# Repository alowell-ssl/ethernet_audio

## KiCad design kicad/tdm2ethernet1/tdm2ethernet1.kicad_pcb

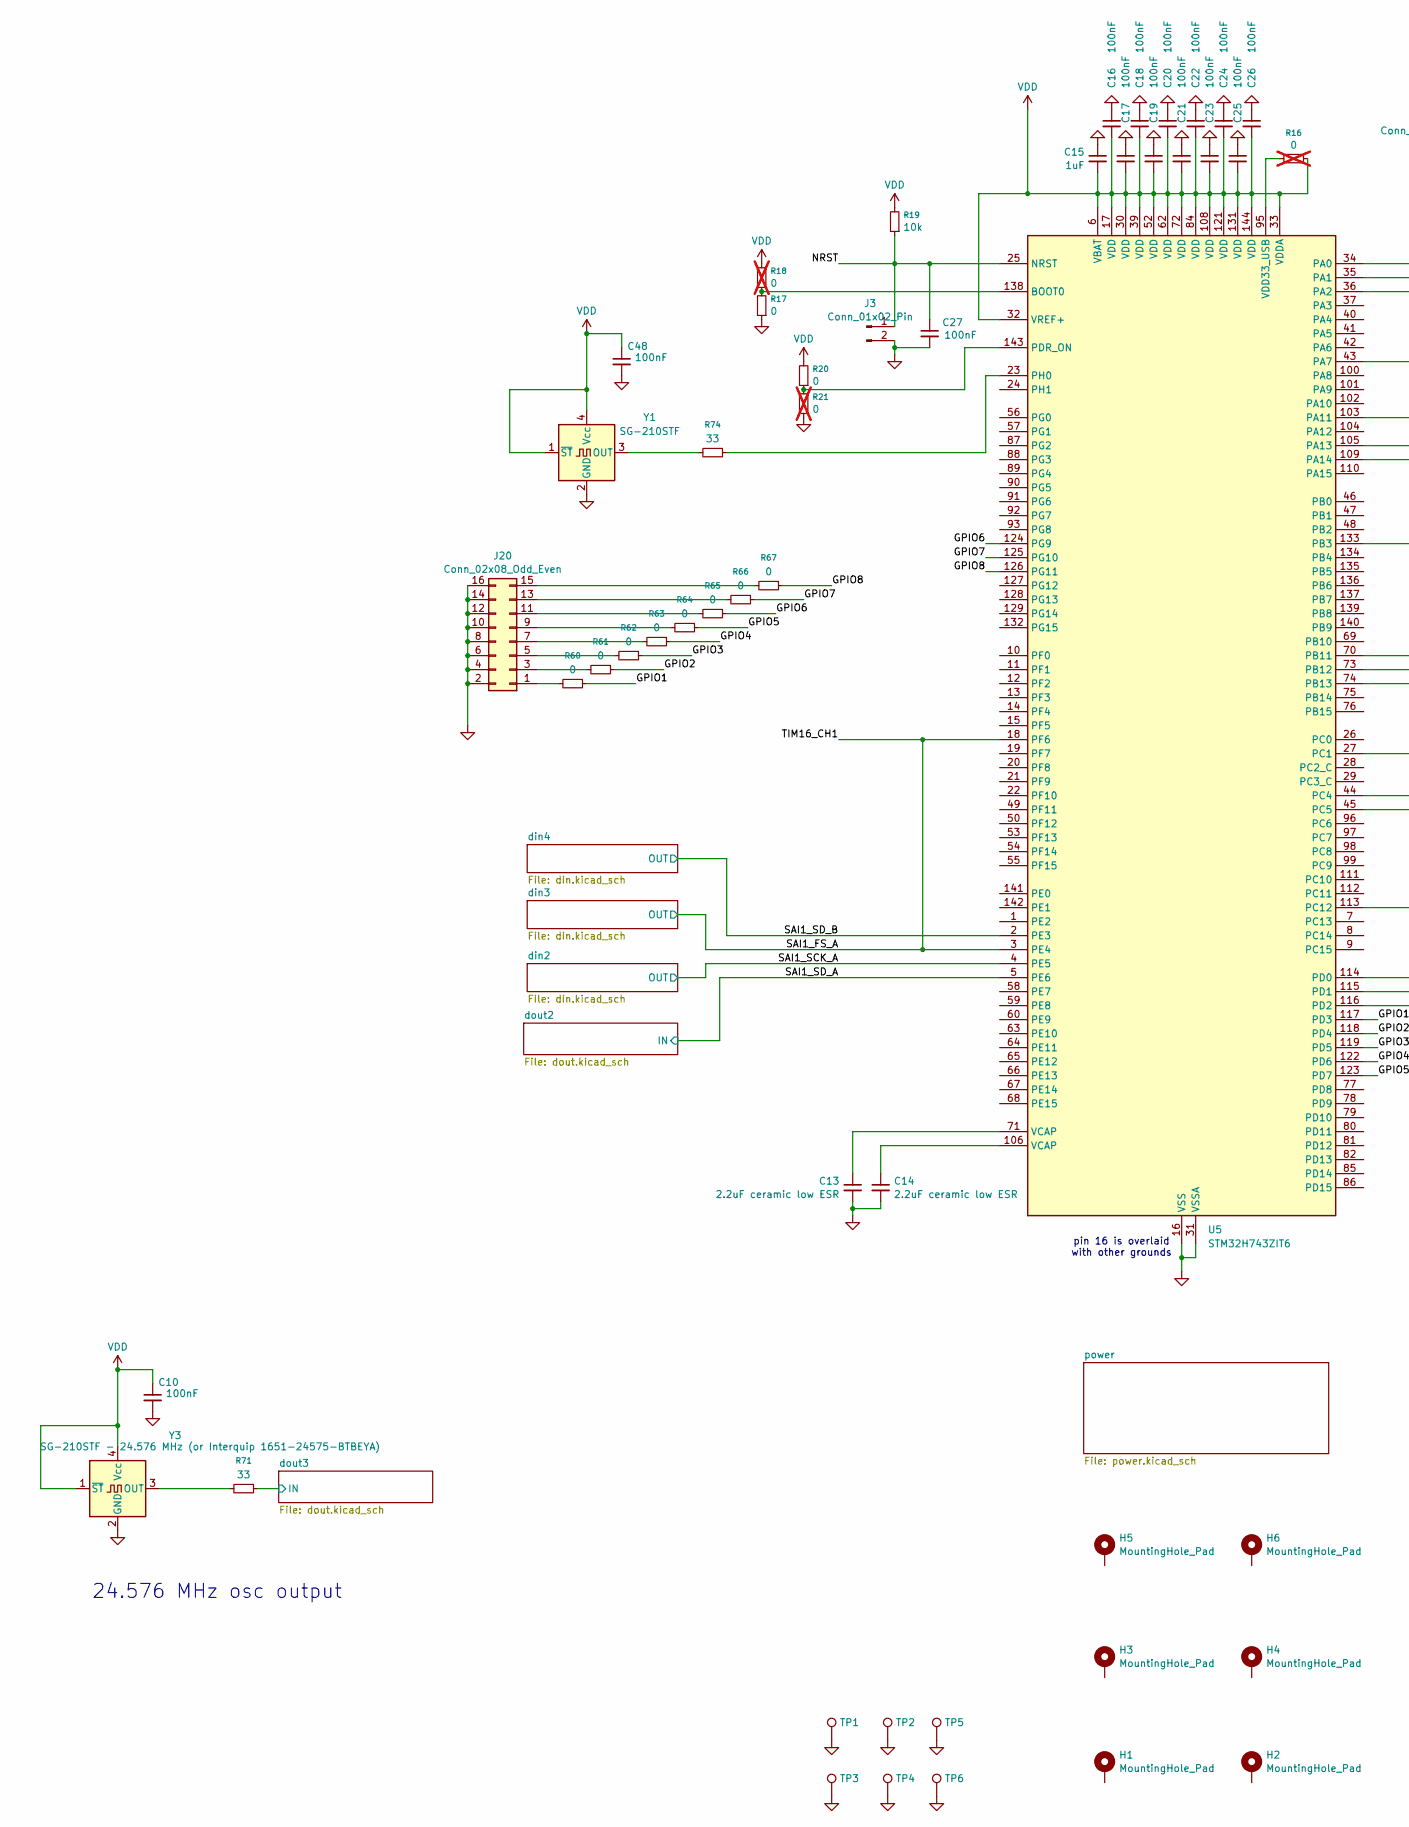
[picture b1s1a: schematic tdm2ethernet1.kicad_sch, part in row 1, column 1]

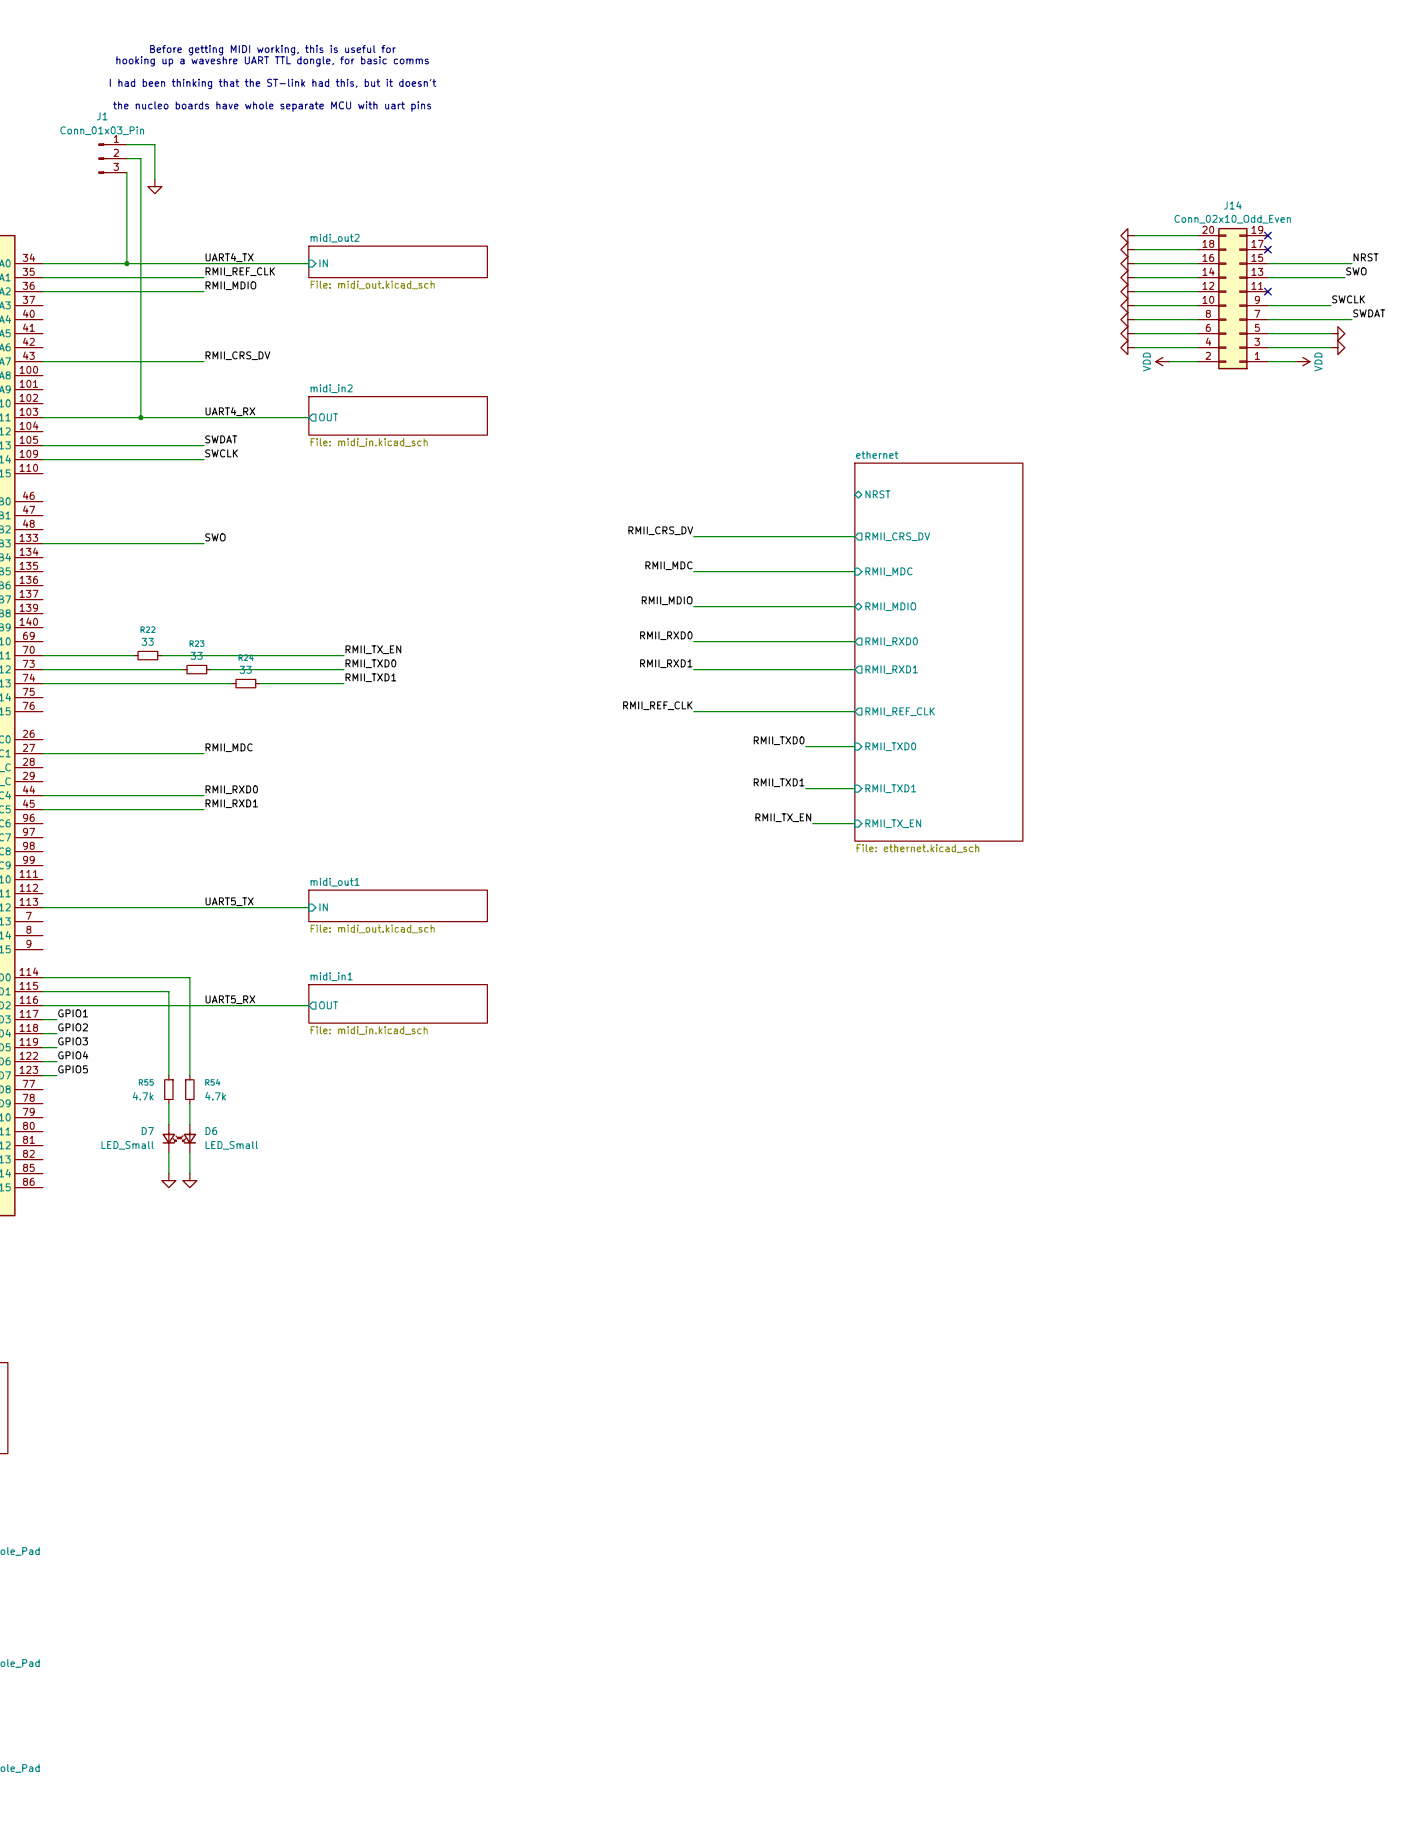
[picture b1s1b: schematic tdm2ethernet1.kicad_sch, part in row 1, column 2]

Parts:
C10, C16, C17, C18, C19, C20, C21, C22, C23, C24, C25, C26, C27, C48: 100nF; C_0603_1608Metric; LCSC Part # C14663
C13, C14: 2.2uF ceramic low ESR; C_0603_1608Metric; LCSC Part # C23630
C15: 1uF; C_0603_1608Metric; LCSC Part # C15849
D6, D7: LED_Small; LED_0603_1608Metric; LCSC Part # C2286
H1, H2, H3, H4, H5, H6: MountingHole_Pad; MountingHole_3.2mm_M3_DIN965
J1: Conn_01x03_Pin; PinHeader_1x03_P2.54mm_Vertical
J3: Conn_01x02_Pin; PinHeader_1x02_P2.54mm_Vertical
J14: Conn_02x10_Odd_Even; PinHeader_2x10_P2.54mm_Vertical
J20: Conn_02x08_Odd_Even; PinSocket_2x08_P2.54mm_Vertical
R16, R18, R21: 0; R_0603_1608Metric; LCSC Part # C21189; not fitted
R17, R20, R60, R61, R62, R63, R64, R65, R66, R67: 0; R_0603_1608Metric; LCSC Part # C21189
R19: 10k; R_0603_1608Metric; LCSC Part # C15401
R22, R23, R24, R71, R74: 33; R_0603_1608Metric; LCSC Part # C23140
R54, R55: 4.7k; R_0603_1608Metric; LCSC Part # C23162
TP1, TP2, TP3, TP4, TP5, TP6: TestPoint; TestPoint_THTPad_D1.5mm_Drill0.7mm
U5: STM32H743ZIT6; LQFP-144_20x20mm_P0.5mm; LCSC Part # C114408
Y1: SG-210STF; Oscillator_SMD_SeikoEpson_SG210-4Pin_2.5x2.0mm; LCSC Part # C70560
Y3: SG-210STF - 24.576 MHz (or Interquip 1651-24575-B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; Oscillator_SMD_SeikoEpson_SG210-4Pin_2.5x2.0mm; LCSC Part # C3003263

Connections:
/GPIO1: R60.1, U5.117 (PD3)
/GPIO2: R61.1, U5.118 (PD4)
/GPIO3: R62.1, U5.119 (PD5)
/GPIO4: R63.1, U5.122 (PD6)
/GPIO5: R64.1, U5.123 (PD7)
/GPIO6: R65.1, U5.124 (PG9)
/GPIO7: R66.1, U5.125 (PG10)
/GPIO8: R67.1, U5.126 (PG11)
/NRST: C27.1, J3.1, J14.15, R19.1, U5.25 (NRST)
/RMII_CRS_DV: U5.43 (PA7); also elsewhere on the board
/RMII_MDC: U5.27 (PC1); also elsewhere on the board
/RMII_MDIO: U5.36 (PA2); also elsewhere on the board
/RMII_REF_CLK: U5.35 (PA1); also elsewhere on the board
/RMII_RXD0: U5.44 (PC4); also elsewhere on the board
/RMII_RXD1: U5.45 (PC5); also elsewhere on the board
/RMII_TXD0: R23.1; also elsewhere on the board
/RMII_TXD1: R24.1; also elsewhere on the board
/RMII_TX_EN: R22.1; also elsewhere on the board
/SAI1_FS_A: U5.3 (PE4), U5.18 (PF6); also elsewhere on the board
/SAI1_SCK_A: U5.4 (PE5); also elsewhere on the board
/SAI1_SD_A: U5.5 (PE6); also elsewhere on the board
/SAI1_SD_B: U5.2 (PE3); also elsewhere on the board
/SWCLK: J14.9, U5.109 (PA14)
/SWDAT: J14.7, U5.105 (PA13)
/SWO: J14.13, U5.133 (PB3)
/UART4_RX: J1.2, U5.103 (PA11); also elsewhere on the board
/UART4_TX: J1.3, U5.34 (PA0); also elsewhere on the board
/UART5_RX: U5.116 (PD2); also elsewhere on the board
/UART5_TX: U5.113 (PC12); also elsewhere on the board
/dout3/IN: R71.1; also elsewhere on the board
GND: C10.2, C13.2, C14.2, C15.1, C16.1, C17.1, C18.1, C19.1, C20.1, C21.1, C22.1, C23.1, C24.1, C25.1, C26.1, C27.2, C48.2, D6.1 (K), D7.1 (K), J1.1, J3.2, J14.3, J14.4, J14.5, J14.6, J14.8, J14.10, J14.12, J14.14, J14.16, J14.18, J14.20, J20.2, J20.4, J20.6, J20.8, J20.10, J20.12, J20.14, J20.16, R17.1, R21.1, TP1.1, TP2.1, TP3.1, TP4.1, TP5.1, TP6.1, U5.16 (VSS), U5.31 (VSSA), U5.38 (VSS), U5.51 (VSS), U5.61 (VSS), U5.83 (VSS), U5.94 (VSS), U5.107 (VSS), U5.120 (VSS), U5.130 (VSS), Y1.2 (GND), Y3.2 (GND); also elsewhere on the board
unnamed: C13.1, U5.71 (VCAP)
unnamed: C14.1, U5.106 (VCAP)
unnamed: D6.2 (A), R54.2
unnamed: D7.2 (A), R55.2
unnamed: J20.1, R60.2
unnamed: J20.3, R61.2
unnamed: J20.5, R62.2
unnamed: J20.7, R63.2
unnamed: J20.9, R64.2
unnamed: J20.11, R65.2
unnamed: J20.13, R66.2
unnamed: J20.15, R67.2
unnamed: R17.2, R18.1, U5.138 (BOOT0)
unnamed: R22.2, U5.70 (PB11)
unnamed: R23.2, U5.73 (PB12)
unnamed: R24.2, U5.74 (PB13)
unnamed: R54.1, U5.114 (PD0)
unnamed: R55.1, U5.115 (PD1)
unnamed: R20.1, R21.2, U5.143 (PDR_ON)
unnamed: R74.1, U5.23 (PH0)
unnamed: R16.1, U5.95 (VDD33_USB)
unnamed: R74.2, Y1.3 (OUT)
unnamed: R71.2, Y3.3 (OUT)
VDD: C10.1, C15.2, C16.2, C17.2, C18.2, C19.2, C20.2, C21.2, C22.2, C23.2, C24.2, C25.2, C26.2, C48.1, J14.1, J14.2, R16.2, R18.2, R19.2, R20.2, U5.6 (VBAT), U5.17 (VDD), U5.30 (VDD), U5.32 (VREF+), U5.33 (VDDA), U5.39 (VDD), U5.52 (VDD), U5.62 (VDD), U5.72 (VDD), U5.84 (VDD), U5.108 (VDD), U5.121 (VDD), U5.131 (VDD), U5.144 (VDD), Y1.1 (~ST), Y1.4 (Vcc), Y3.1 (~ST), Y3.4 (Vcc); also elsewhere on the board

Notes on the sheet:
24.576 MHz osc output
pin 16 is overlaid with other grounds
Before getting MIDI working, this is useful for hooking up a waveshre UART TTL dongle, for basic comms I had been thinking that the ST-link had this, but it doesn't the nucleo boards have whole separate MCU with uart pins

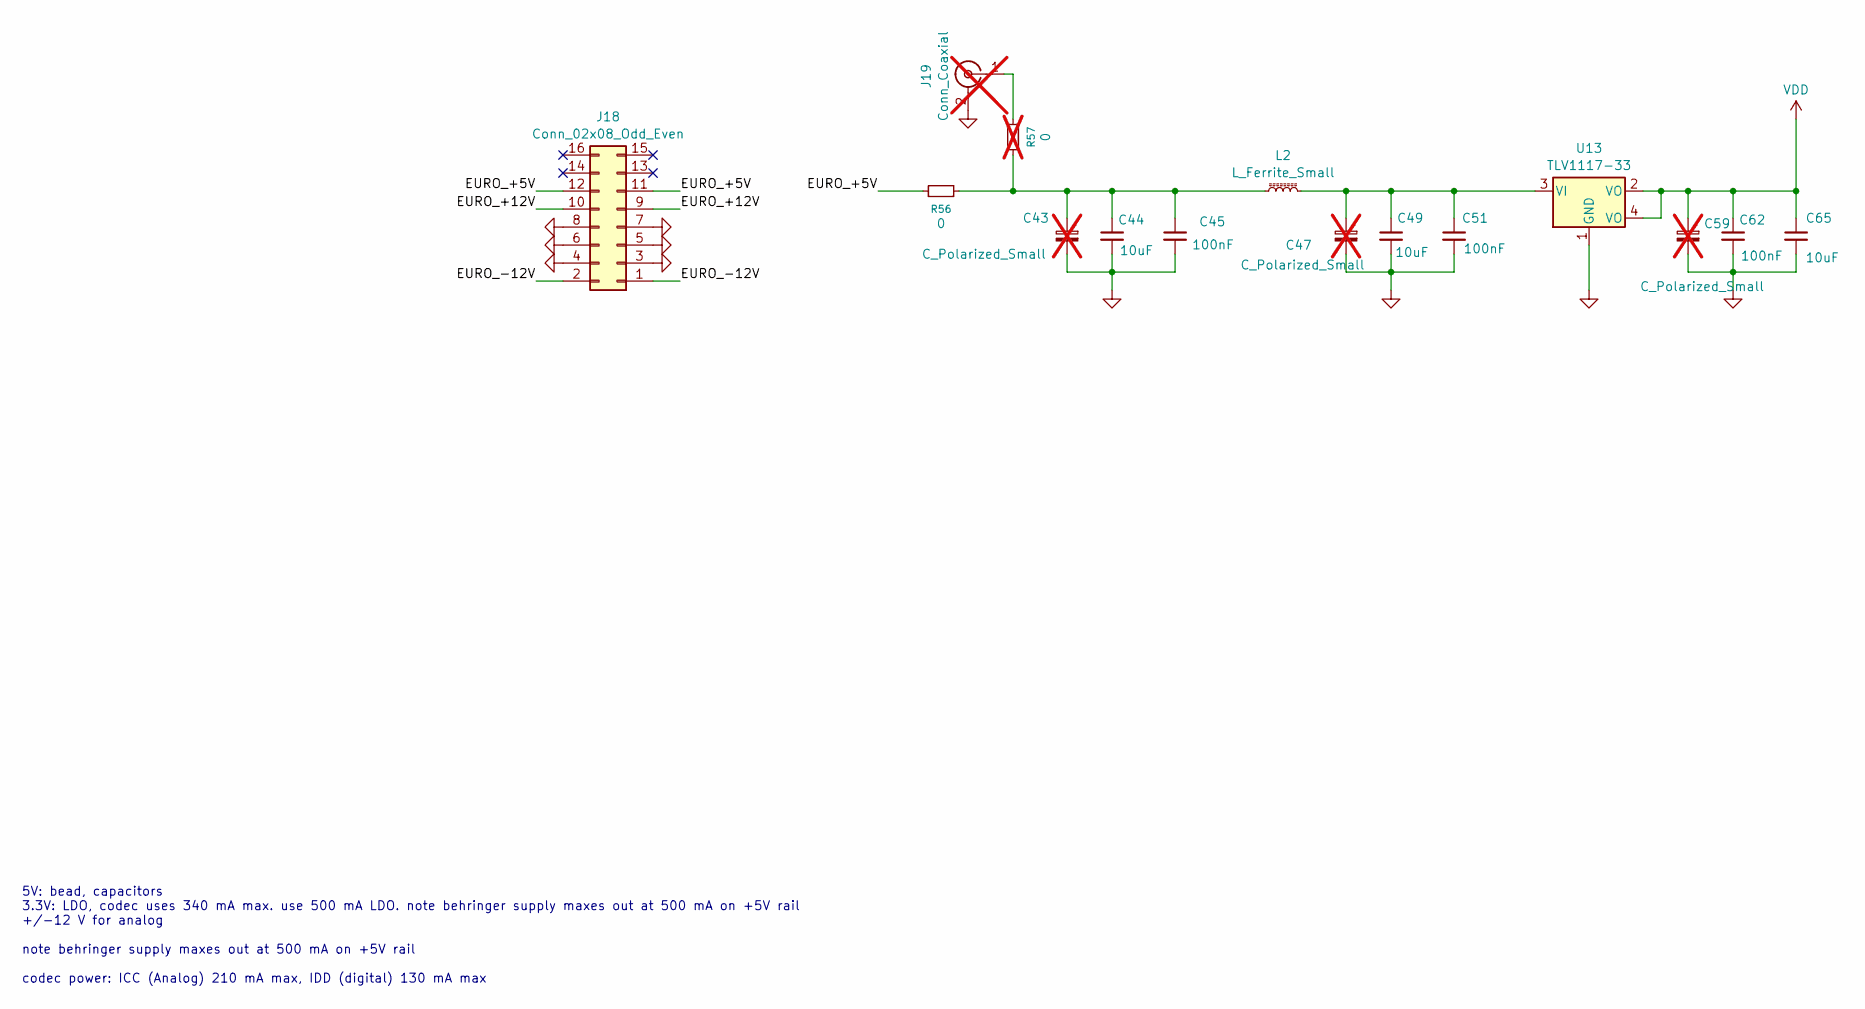
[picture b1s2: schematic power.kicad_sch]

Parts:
C43, C47, C59: C_Polarized_Small; CP_Radial_D8.0mm_P3.50mm; not fitted
C44, C49, C65: 10uF; C_0603_1608Metric; LCSC Part # C96446
C45, C51, C62: 100nF; C_0603_1608Metric; LCSC Part # C14663
J18: Conn_02x08_Odd_Even; PinSocket_2x08_P2.54mm_Vertical
J19: Conn_Coaxial; SMA_Amphenol_901-144_Vertical; not fitted
L2: L_Ferrite_Small; L_0603_1608Metric; LCSC Part # C1002
R56: 0; R_0603_1608Metric; LCSC Part # C21189
R57: 0; R_0603_1608Metric; LCSC Part # C21189; not fitted
U13: TLV1117-33; SOT-223

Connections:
/power/EURO_+5V: J18.11, J18.12, R56.1
/power/EURO_+12V: J18.9, J18.10
/power/EURO_-12V: J18.1, J18.2
GND: C43.2, C44.2, C45.2, C47.2, C49.2, C51.2, C59.2, C62.2, C65.2, J18.3, J18.4, J18.5, J18.6, J18.7, J18.8, J19.2 (Ext), U13.1 (GND); also elsewhere on the board
unnamed: C43.1, C44.1, C45.1, L2.1, R56.2, R57.1
unnamed: J19.1 (In), R57.2
unnamed: C47.1, C49.1, C51.1, L2.2, U13.3 (VI)
VDD: C59.1, C62.1, C65.1, U13.2 (VO), U13.4 (VO); also elsewhere on the board

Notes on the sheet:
5V: bead, capacitors 3.3V: LDO, codec uses 340 mA max. use 500 mA LDO. note behringer supply maxes out at 500 mA on +5V rail +/-12 V for analog note behringer supply maxes out at 500 mA on +5V rail codec power: ICC (Analog) 210 mA max, IDD (digital) 130 mA max

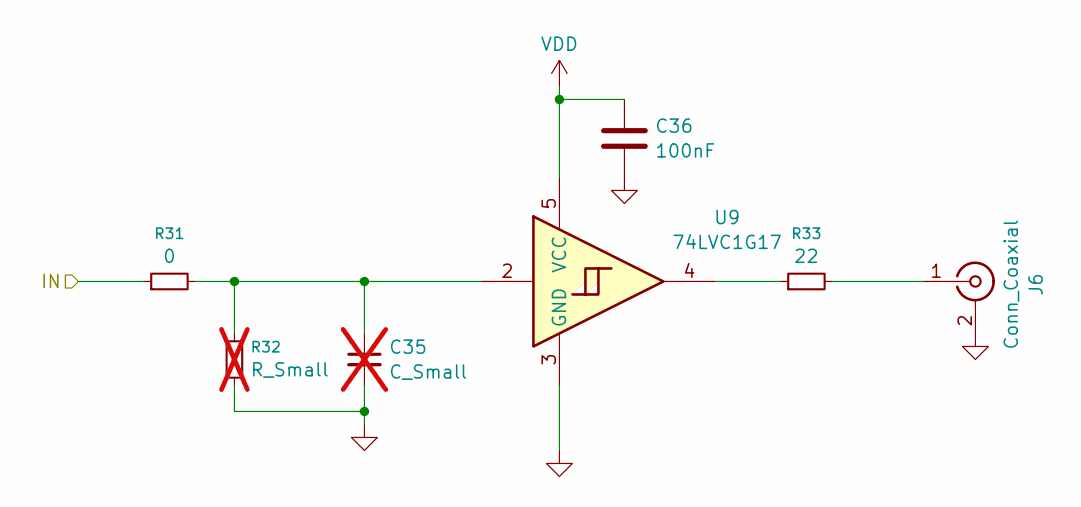
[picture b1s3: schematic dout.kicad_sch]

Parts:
C35: C_Small; C_0603_1608Metric; not fitted
C36: 100nF; C_0603_1608Metric; LCSC Part # C14663
J6: Conn_Coaxial; SMA_Amphenol_901-144_Vertical
R31: 0; R_0603_1608Metric; LCSC Part # C21189
R32: R_Small; R_0603_1608Metric; not fitted
R33: 22; R_0603_1608Metric; LCSC Part # C23345
U9: 74LVC1G17; SOT-23-5; LCSC Part # C7836

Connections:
/SAI1_SD_A: R31.1; also elsewhere on the board
GND: C35.2, C36.2, J6.2 (Ext), R32.1, U9.3 (GND); also elsewhere on the board
unnamed: C35.1, R31.2, R32.2, U9.2
unnamed: J6.1 (In), R33.2
unnamed: R33.1, U9.4
VDD: C36.1, U9.5 (VCC); also elsewhere on the board

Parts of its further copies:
C12: C_Small; C_0603_1608Metric; not fitted
C52: 100nF; C_0603_1608Metric; LCSC Part # C14663
J2: Conn_Coaxial; SMA_Amphenol_901-144_Vertical
R72: 0; R_0603_1608Metric; LCSC Part # C21189
R73: R_Small; R_0603_1608Metric; not fitted
R76: 22; R_0603_1608Metric; LCSC Part # C23345
U14: 74LVC1G17; SOT-23-5; LCSC Part # C7836

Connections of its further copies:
/dout3/IN: R72.1; also elsewhere on the board
GND: C12.2, C52.2, J2.2 (Ext), R73.1, U14.3 (GND); also elsewhere on the board
unnamed: C12.1, R72.2, R73.2, U14.2
unnamed: J2.1 (In), R76.2
unnamed: R76.1, U14.4
VDD: C52.1, U14.5 (VCC); also elsewhere on the board

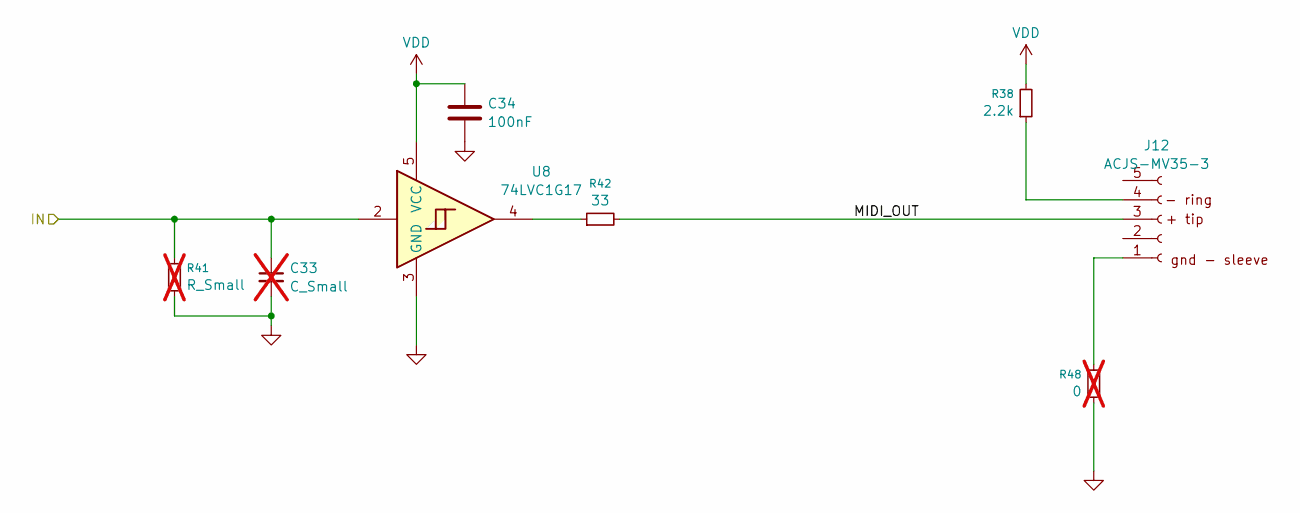
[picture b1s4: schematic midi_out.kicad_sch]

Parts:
C33: C_Small; C_0603_1608Metric; not fitted
C34: 100nF; C_0603_1608Metric; LCSC Part # C14663
J12: ACJS-MV35-3; Amphenol_ACJS
R38: 2.2k; R_0603_1608Metric; LCSC Part # C4190
R41: R_Small; R_0603_1608Metric; not fitted
R42: 33; R_0603_1608Metric; LCSC Part # C23140
R48: 0; R_0603_1608Metric; LCSC Part # C21189; not fitted
U8: 74LVC1G17; SOT-23-5; LCSC Part # C7836

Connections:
/UART5_TX: C33.1, R41.2, U8.2; also elsewhere on the board
/midi_out1/MIDI_OUT: J12.3, R42.2
GND: C33.2, C34.2, R41.1, R48.1, U8.3 (GND); also elsewhere on the board
unnamed: J12.1, R48.2
unnamed: J12.4, R38.1
unnamed: R42.1, U8.4
VDD: C34.1, R38.2, U8.5 (VCC); also elsewhere on the board

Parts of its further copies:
C29: C_Small; C_0603_1608Metric; not fitted
C30: 100nF; C_0603_1608Metric; LCSC Part # C14663
J13: ACJS-MV35-3; Amphenol_ACJS
R28: R_Small; R_0603_1608Metric; not fitted
R29: 33; R_0603_1608Metric; LCSC Part # C23140
R30: 2.2k; R_0603_1608Metric; LCSC Part # C4190
R49: 0; R_0603_1608Metric; LCSC Part # C21189; not fitted
U6: 74LVC1G17; SOT-23-5; LCSC Part # C7836

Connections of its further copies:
/UART4_TX: C29.1, R28.2, U6.2; also elsewhere on the board
/midi_out2/MIDI_OUT: J13.3, R29.2
GND: C29.2, C30.2, R28.1, R49.1, U6.3 (GND); also elsewhere on the board
unnamed: J13.1, R49.2
unnamed: J13.4, R30.1
unnamed: R29.1, U6.4
VDD: C30.1, R30.2, U6.5 (VCC); also elsewhere on the board

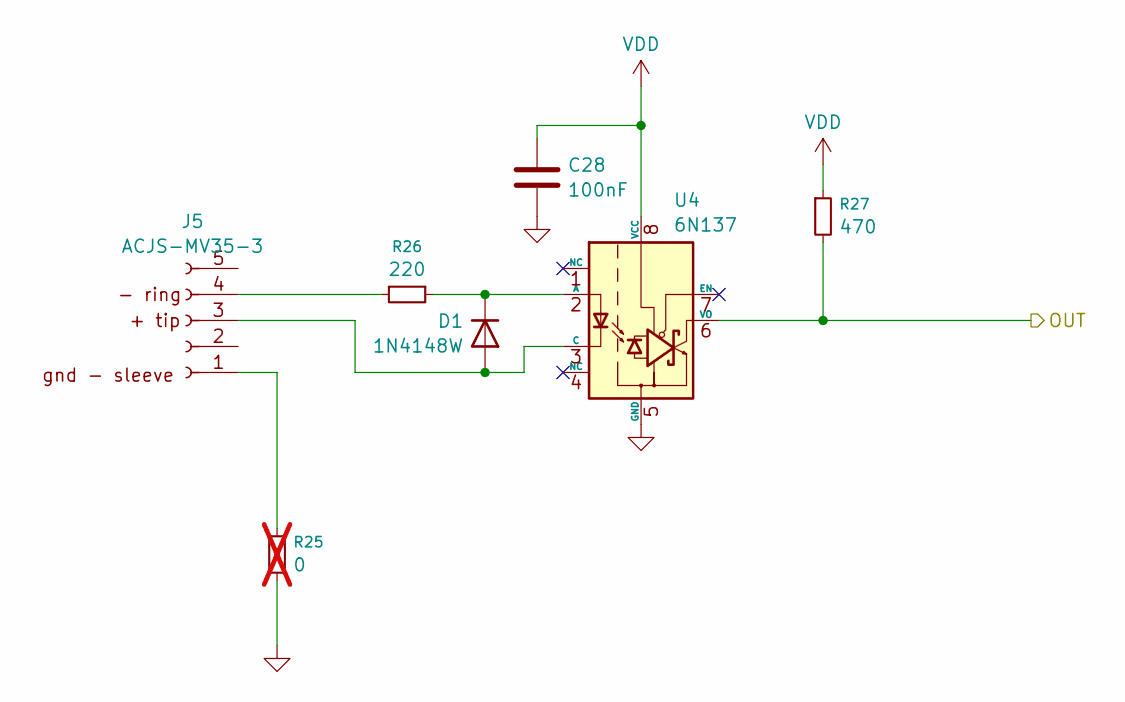
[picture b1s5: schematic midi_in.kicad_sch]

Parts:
C28: 100nF; C_0603_1608Metric; LCSC Part # C14663
D1: 1N4148W; D_SOD-123; LCSC Part # C81598
J5: ACJS-MV35-3; Amphenol_ACJS
R25: 0; R_0603_1608Metric; LCSC Part # C21189; not fitted
R26: 220; R_0603_1608Metric; LCSC Part # C22962
R27: 470; R_0603_1608Metric; LCSC Part # C23179
U4: 6N137; DIP-8_W7.62mm

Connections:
/UART4_RX: R27.2, U4.6 (VO); also elsewhere on the board
GND: C28.2, R25.1, U4.5 (GND); also elsewhere on the board
unnamed: D1.2 (A), J5.3, U4.3 (C)
unnamed: D1.1 (K), R26.1, U4.2 (A)
unnamed: J5.1, R25.2
unnamed: J5.4, R26.2
VDD: C28.1, R27.1, U4.8 (VCC); also elsewhere on the board

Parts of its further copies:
C32: 100nF; C_0603_1608Metric; LCSC Part # C14663
D5: 1N4148W; D_SOD-123; LCSC Part # C81598
J10: ACJS-MV35-3; Amphenol_ACJS
R44: 220; R_0603_1608Metric; LCSC Part # C22962
R45: 470; R_0603_1608Metric; LCSC Part # C23179
R50: 0; R_0603_1608Metric; LCSC Part # C21189; not fitted
U7: 6N137; DIP-8_W7.62mm

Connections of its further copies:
/UART5_RX: R45.2, U7.6 (VO); also elsewhere on the board
GND: C32.2, R50.1, U7.5 (GND); also elsewhere on the board
unnamed: D5.2 (A), J10.3, U7.3 (C)
unnamed: D5.1 (K), R44.1, U7.2 (A)
unnamed: J10.1, R50.2
unnamed: J10.4, R44.2
VDD: C32.1, R45.1, U7.8 (VCC); also elsewhere on the board

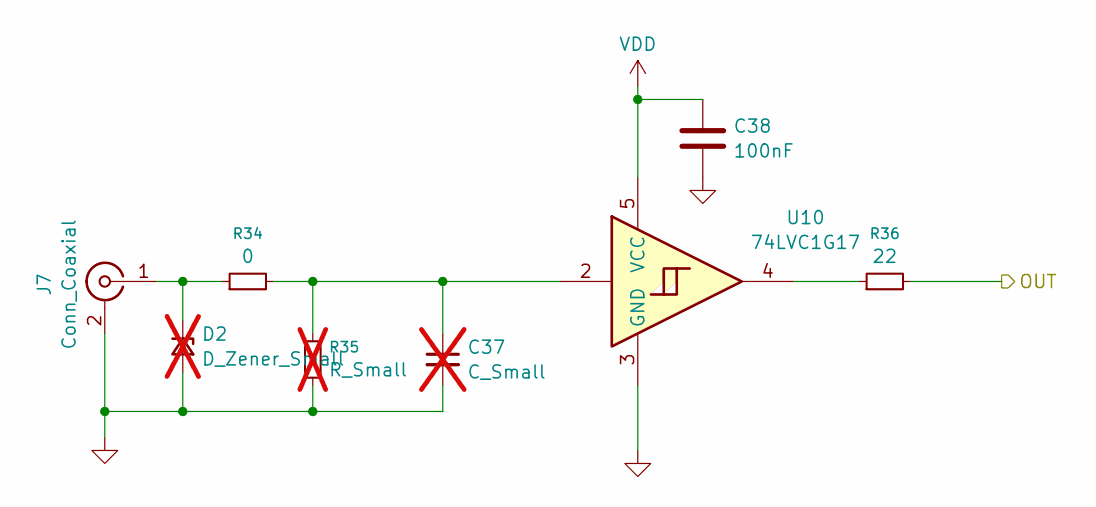
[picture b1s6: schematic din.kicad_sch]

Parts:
C37: C_Small; C_0603_1608Metric; not fitted
C38: 100nF; C_0603_1608Metric; LCSC Part # C14663
D2: D_Zener_Small; D_SOD-123F; not fitted
J7: Conn_Coaxial; SMA_Amphenol_901-144_Vertical
R34: 0; R_0603_1608Metric; LCSC Part # C21189
R35: R_Small; R_0603_1608Metric; not fitted
R36: 22; R_0603_1608Metric; LCSC Part # C23345
U10: 74LVC1G17; SOT-23-5; LCSC Part # C7836

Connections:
/SAI1_SCK_A: R36.2; also elsewhere on the board
GND: C37.2, C38.2, D2.2 (A), J7.2 (Ext), R35.1, U10.3 (GND); also elsewhere on the board
unnamed: C37.1, R34.2, R35.2, U10.2
unnamed: D2.1 (K), J7.1 (In), R34.1
unnamed: R36.1, U10.4
VDD: C38.1, U10.5 (VCC); also elsewhere on the board

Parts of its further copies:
C39, C41: C_Small; C_0603_1608Metric; not fitted
C40, C42: 100nF; C_0603_1608Metric; LCSC Part # C14663
D3, D4: D_Zener_Small; D_SOD-123F; not fitted
J8, J11: Conn_Coaxial; SMA_Amphenol_901-144_Vertical
R37, R43: 0; R_0603_1608Metric; LCSC Part # C21189
R39, R46: R_Small; R_0603_1608Metric; not fitted
R40, R47: 22; R_0603_1608Metric; LCSC Part # C23345
U11, U12: 74LVC1G17; SOT-23-5; LCSC Part # C7836

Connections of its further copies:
/SAI1_FS_A: R40.2; also elsewhere on the board
/SAI1_SD_B: R47.2; also elsewhere on the board
GND: C39.2, C40.2, C41.2, C42.2, D3.2 (A), D4.2 (A), J8.2 (Ext), J11.2 (Ext), R39.1, R46.1, U11.3 (GND), U12.3 (GND); also elsewhere on the board
unnamed: C39.1, R37.2, R39.2, U11.2
unnamed: C41.1, R43.2, R46.2, U12.2
unnamed: D3.1 (K), J8.1 (In), R37.1
unnamed: D4.1 (K), J11.1 (In), R43.1
unnamed: R40.1, U11.4
unnamed: R47.1, U12.4
VDD: C40.1, C42.1, U11.5 (VCC), U12.5 (VCC); also elsewhere on the board

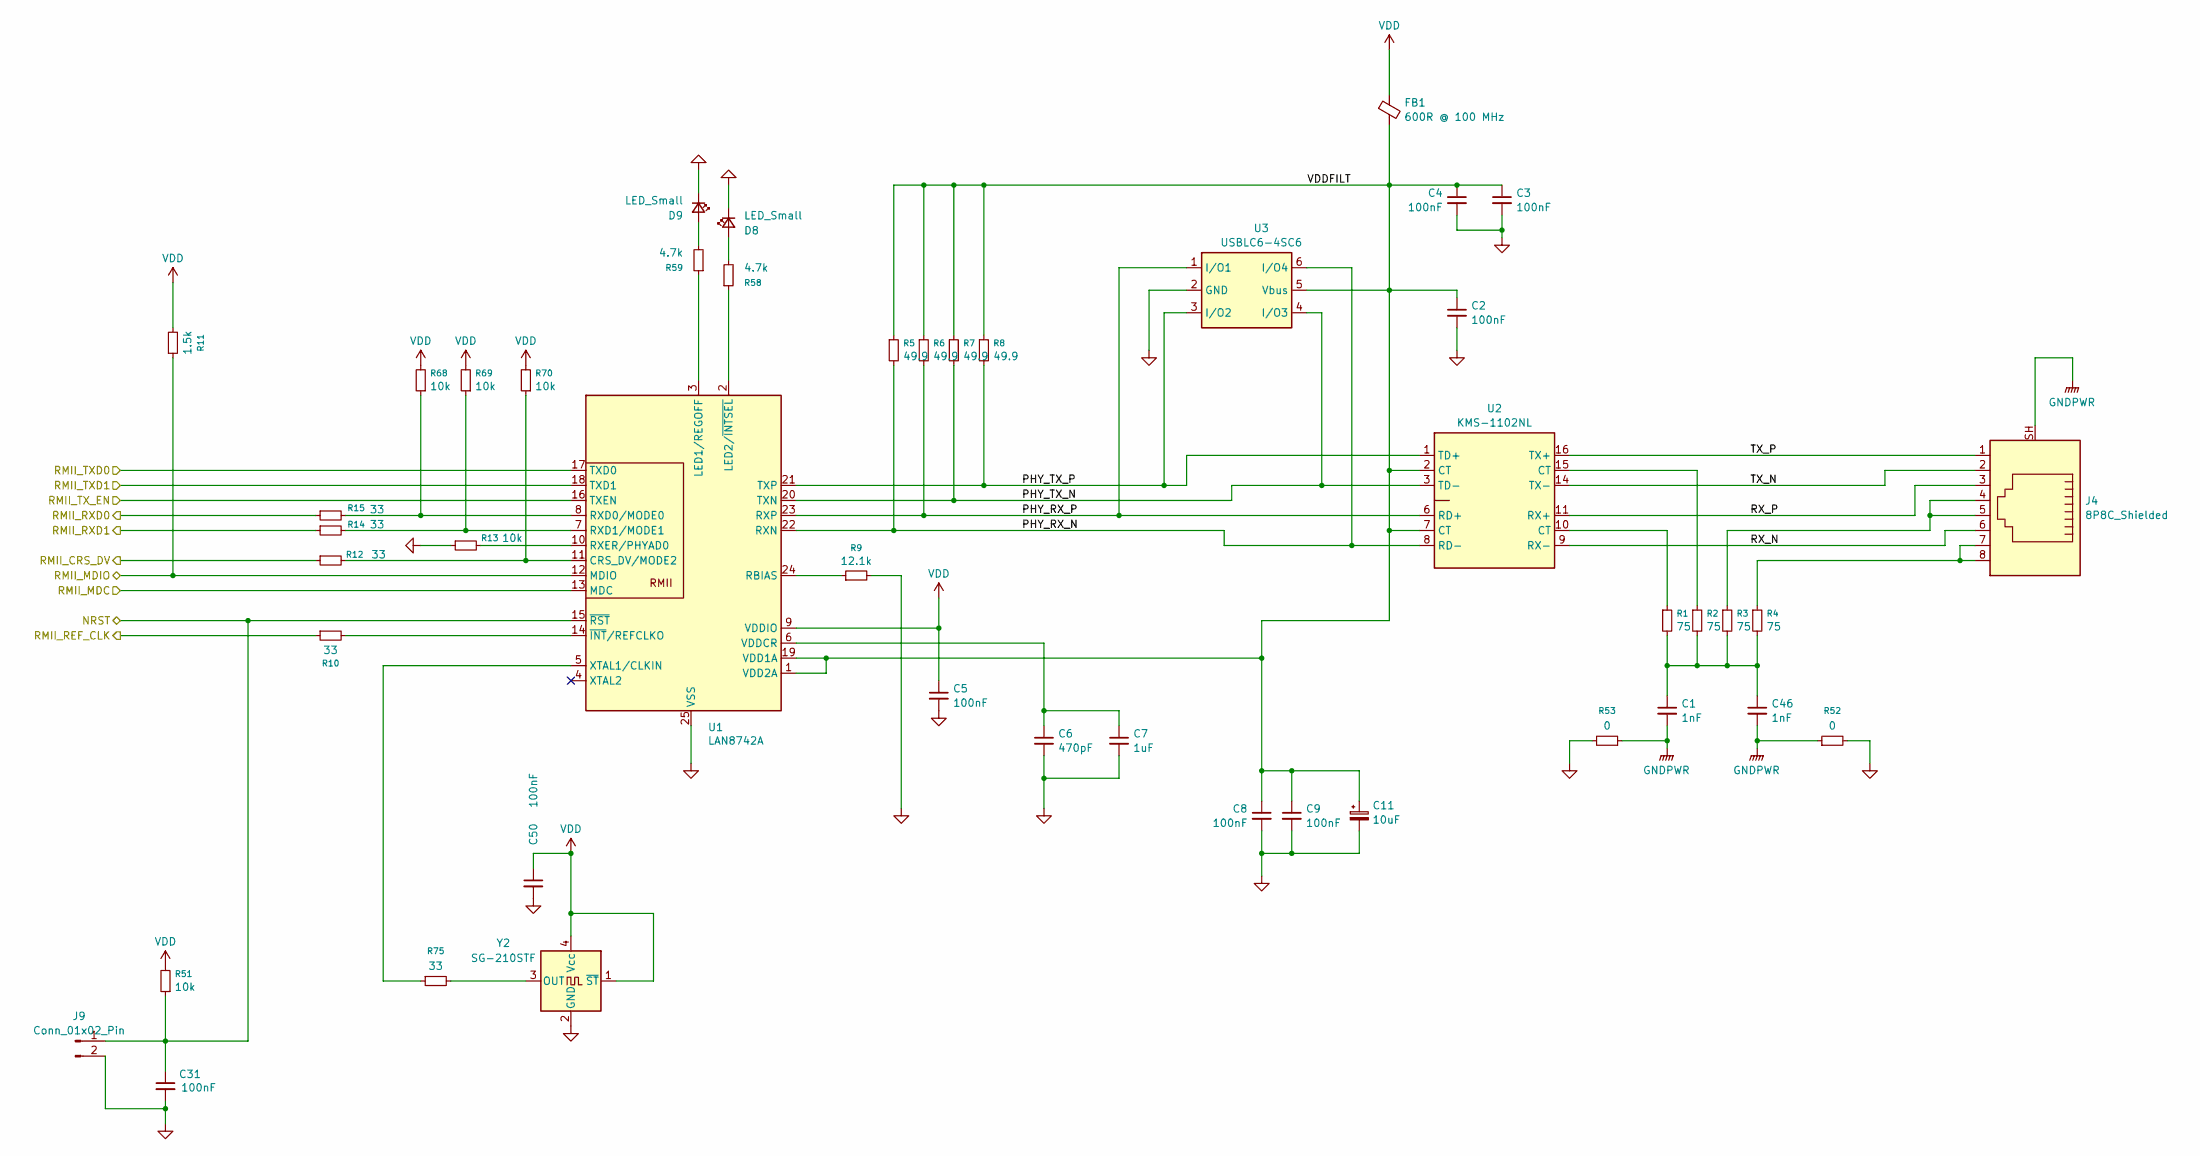
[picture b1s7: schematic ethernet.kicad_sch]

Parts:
C1, C46: 1nF; C_0603_1608Metric; LCSC Part # C1588
C2, C3, C4, C5, C8, C9, C31, C50: 100nF; C_0603_1608Metric; LCSC Part # C14663
C6: 470pF; C_0603_1608Metric; LCSC Part # C1620
C7: 1uF; C_0603_1608Metric; LCSC Part # C15849
C11: 10uF; C_1206_3216Metric; LCSC Part # C13585
D8, D9: LED_Small; LED_0603_1608Metric; LCSC Part # C2286
FB1: 600R @ 100 MHz; L_0603_1608Metric; LCSC Part # C1002
J4: 8P8C_Shielded; A-2014-2S-4-N-R
J9: Conn_01x02_Pin; PinHeader_1x02_P2.54mm_Vertical
R1, R2, R3, R4: 75; R_0603_1608Metric; LCSC Part # C4275
R5, R6, R7, R8: 49.9; R_0603_1608Metric; LCSC Part # C23185
R9: 12.1k; R_0603_1608Metric
R10, R12, R14, R15, R75: 33; R_0603_1608Metric; LCSC Part # C23140
R11: 1.5k; R_0603_1608Metric; LCSC Part # C22843
R13, R51, R68, R69, R70: 10k; R_0603_1608Metric; LCSC Part # C15401
R52, R53: 0; R_0603_1608Metric; LCSC Part # C21189
R58, R59: 4.7k; R_0603_1608Metric; LCSC Part # C23162
U1: LAN8742A; VQFN-24-1EP_4x4mm_P0.5mm_EP2.5x2.5mm_ThermalVias; LCSC Part # C621424
U2: KMS-1102NL; Untitled
U3: USBLC6-4SC6; SOT-23-6
Y2: SG-210STF; Oscillator_SMD_SeikoEpson_SG210-4Pin_2.5x2.0mm; LCSC Part # C70560

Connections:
/RMII_CRS_DV: R12.1; also elsewhere on the board
/RMII_MDC: U1.13 (MDC); also elsewhere on the board
/RMII_MDIO: R11.1, U1.12 (MDIO); also elsewhere on the board
/RMII_REF_CLK: R10.1; also elsewhere on the board
/RMII_RXD0: R15.1; also elsewhere on the board
/RMII_RXD1: R14.1; also elsewhere on the board
/RMII_TXD0: U1.17 (TXD0); also elsewhere on the board
/RMII_TXD1: U1.18 (TXD1); also elsewhere on the board
/RMII_TX_EN: U1.16 (TXEN); also elsewhere on the board
/ethernet/NRST: C31.1, J9.1, R51.1, U1.15 (~RST)
/ethernet/PHY_RX_N: R5.2, U1.22 (RXN), U2.8 (RD-), U3.6 (I/O4)
/ethernet/PHY_RX_P: R6.2, U1.23 (RXP), U2.6 (RD+), U3.1 (I/O1)
/ethernet/PHY_TX_N: R7.2, U1.20 (TXN), U2.3 (TD-), U3.4 (I/O3)
/ethernet/PHY_TX_P: R8.2, U1.21 (TXP), U2.1 (TD+), U3.3 (I/O2)
/ethernet/RX_N: J4.6, U2.9 (RX-)
/ethernet/RX_P: J4.3, U2.11 (RX+)
/ethernet/TX_N: J4.2, U2.14 (TX-)
/ethernet/TX_P: J4.1, U2.16 (TX+)
/ethernet/VDDFILT: C2.1, C3.1, C4.1, C8.1, C9.1, C11.1, FB1.2, R5.1, R6.1, R7.1, R8.1, U1.1 (VDD2A), U1.19 (VDD1A), U2.2 (CT), U2.7 (CT), U3.5 (Vbus)
GND: C2.2, C3.2, C4.2, C5.2, C6.2, C7.2, C8.2, C9.2, C11.2, C31.2, C50.2, D8.1 (K), D9.1 (K), J9.2, R9.2, R13.1, R52.2, R53.2, U1.25 (VSS), U3.2 (GND), Y2.2 (GND); also elsewhere on the board
GNDPWR: C1.2, C46.2, J4.SH, R52.1, R53.1
unnamed: C1.1, C46.1, R1.2, R2.2, R3.2, R4.2
unnamed: D8.2 (A), R58.2
unnamed: D9.2 (A), R59.2
unnamed: J4.4, J4.5, R3.1
unnamed: J4.7, J4.8, R4.1
unnamed: R1.1, U2.10 (CT)
unnamed: R2.1, U2.15 (CT)
unnamed: R12.2, R70.1, U1.11 (CRS_DV/MODE2)
unnamed: R59.1, U1.3 (LED1/REGOFF)
unnamed: R58.1, U1.2 (LED2/~INTSEL)
unnamed: R9.1, U1.24 (RBIAS)
unnamed: R15.2, R68.1, U1.8 (RXD0/MODE0)
unnamed: R14.2, R69.1, U1.7 (RXD1/MODE1)
unnamed: R13.2, U1.10 (RXER/PHYAD0)
unnamed: C6.1, C7.1, U1.6 (VDDCR)
unnamed: R75.1, U1.5 (XTAL1/CLKIN)
unnamed: R10.2, U1.14 (~INT/REFCLKO)
unnamed: R75.2, Y2.3 (OUT)
VDD: C5.1, C50.1, FB1.1, R11.2, R51.2, R68.2, R69.2, R70.2, U1.9 (VDDIO), Y2.1 (~ST), Y2.4 (Vcc); also elsewhere on the board
